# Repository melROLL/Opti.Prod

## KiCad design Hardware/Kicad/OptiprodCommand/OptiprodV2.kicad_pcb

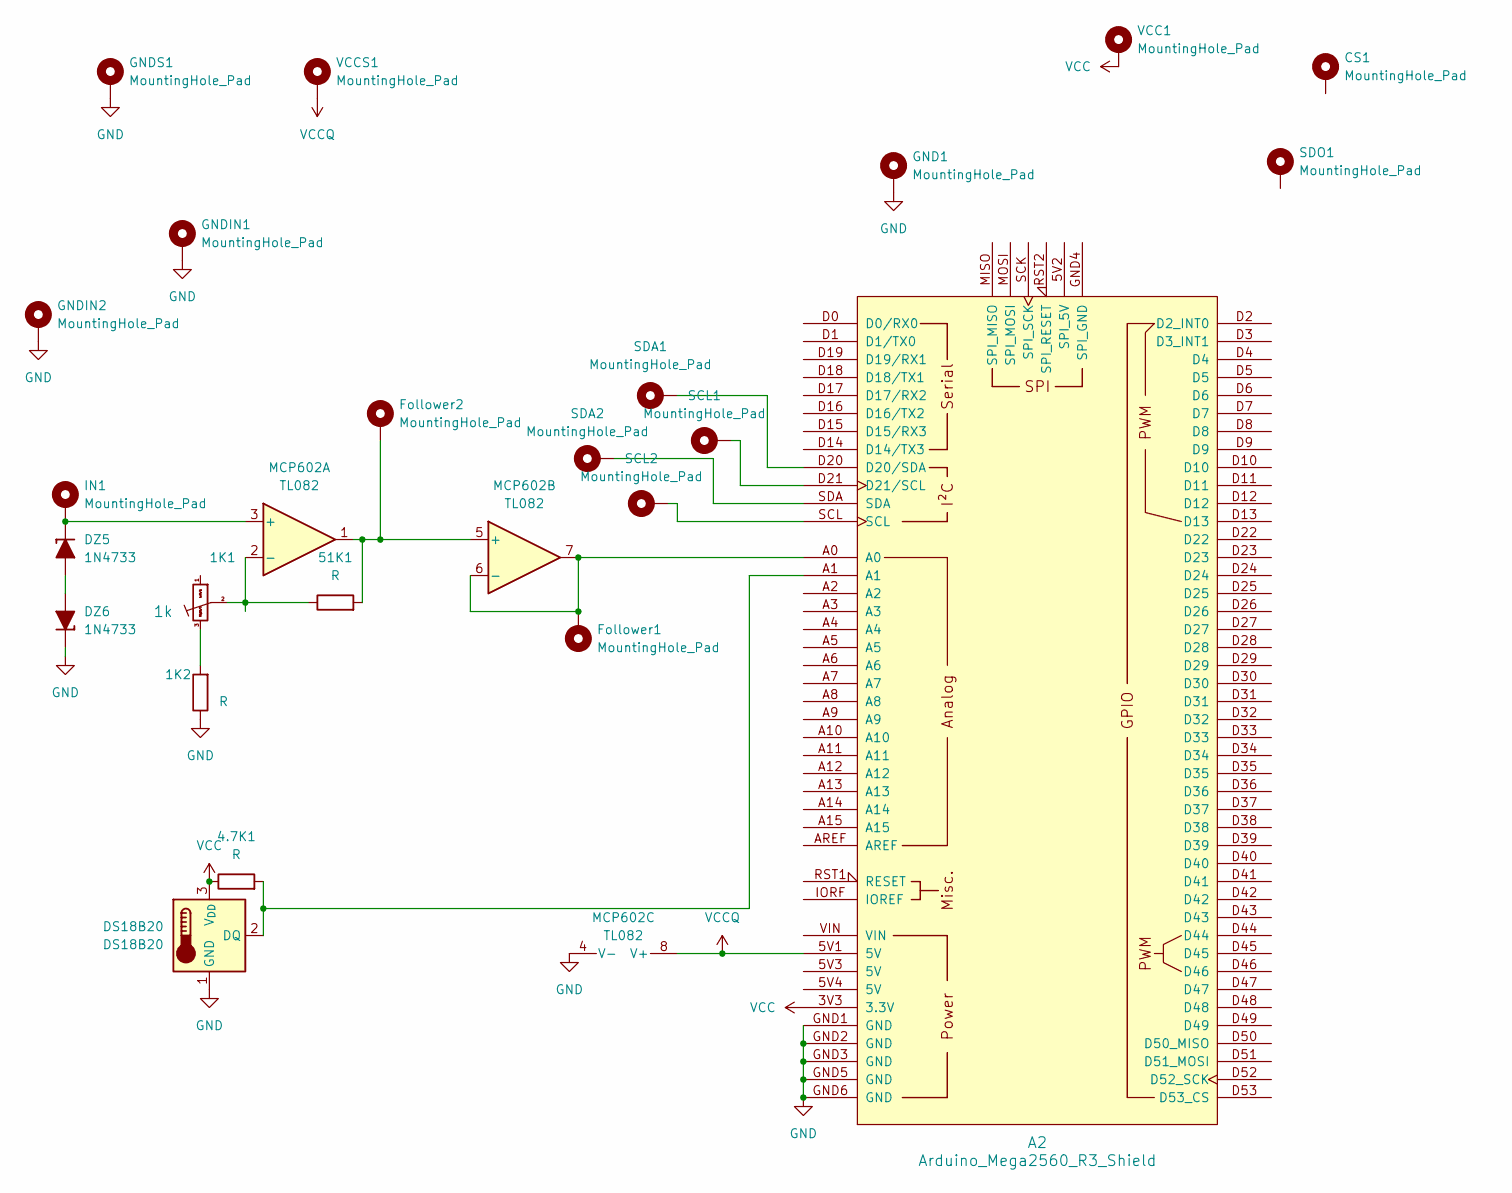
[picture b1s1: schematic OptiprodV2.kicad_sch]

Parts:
1K1: TrimPot_T73YEt_1k; Potentiometer_Bourns_3296W_Vertical; Part Number T73YE102KT20
1K2, 4.7K1, 51K1: R; R_Axial_DIN0204_L3.6mm_D1.6mm_P7.62mm_Horizontal
A2: Arduino_Mega2560_R3_Shield
CS1: MountingHole_Pad; Pin_D1.0mm_L10.0mm
DS18B20: DS18B20; TO-92_Inline_Wide
DZ5, DZ6: 1N4733; D_A-405_P12.70mm_Horizontal
Follower1, Follower2: MountingHole_Pad; Pin_D1.0mm_L10.0mm
GND1: MountingHole_Pad; Pin_D1.0mm_L10.0mm
GNDIN1, GNDIN2: MountingHole_Pad; Pin_D1.0mm_L10.0mm
GNDS1: MountingHole_Pad; Pin_D1.0mm_L10.0mm
IN1: MountingHole_Pad; Pin_D1.0mm_L10.0mm
MCP602: TL082; DIP-8_W7.62mm
SCL1, SCL2: MountingHole_Pad; Pin_D1.0mm_L10.0mm
SDA1, SDA2: MountingHole_Pad; Pin_D1.0mm_L10.0mm
SDO1: MountingHole_Pad; Pin_D1.0mm_L10.0mm
VCC1: MountingHole_Pad; Pin_D1.0mm_L10.0mm
VCCS1: MountingHole_Pad; Pin_D1.0mm_L10.0mm

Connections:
GND: 1K2.1, A2.GND1 (GND), A2.GND2 (GND), A2.GND3 (GND), A2.GND5 (GND), A2.GND6 (GND), DS18B20.1 (GND), DZ6.1 (K), GND1.1, GNDIN1.1, GNDIN2.1, GNDS1.1, MCP602.4 (V-)
unnamed: 1K1.2 (Center), 51K1.1, MCP602.2 (-)
unnamed: 1K1.3 (Right), 1K2.2
unnamed: A2.D20 (D20/SDA), SDA1.1
unnamed: A2.D21 (D21/SCL), SCL1.1
unnamed: A2.SCL, SCL2.1
unnamed: A2.SDA, SDA2.1
unnamed: 4.7K1.2, A2.A1, DS18B20.2 (DQ)
unnamed: DZ5.2 (A), DZ6.2 (A)
unnamed: DZ5.1 (K), IN1.1, MCP602.3 (+)
unnamed: 51K1.2, Follower2.1, MCP602.1, MCP602.5 (+)
unnamed: A2.A0, Follower1.1, MCP602.6 (-), MCP602.7
VCC: 4.7K1.1, A2.3V3 (3.3V), DS18B20.3 (V_{DD}), VCC1.1
VCCQ: A2.5V1 (5V), MCP602.8 (V+), VCCS1.1

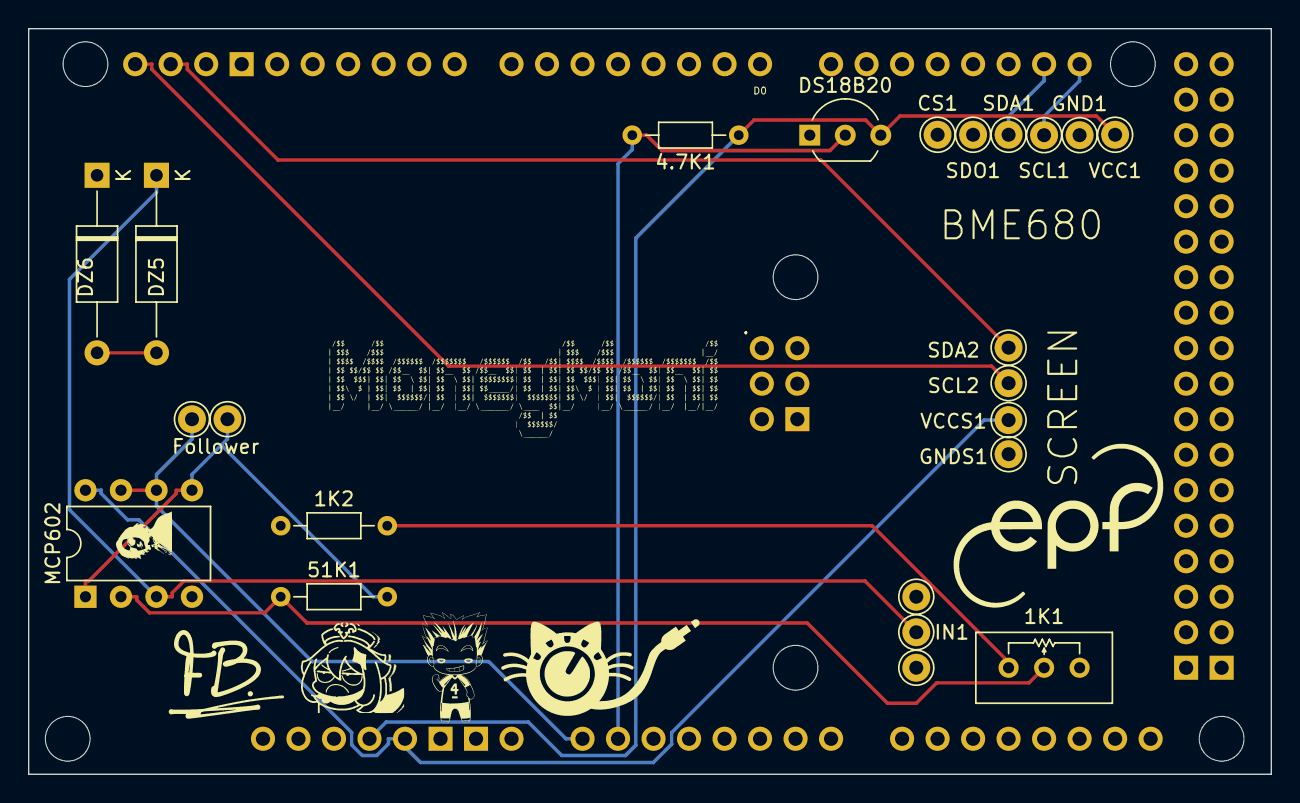
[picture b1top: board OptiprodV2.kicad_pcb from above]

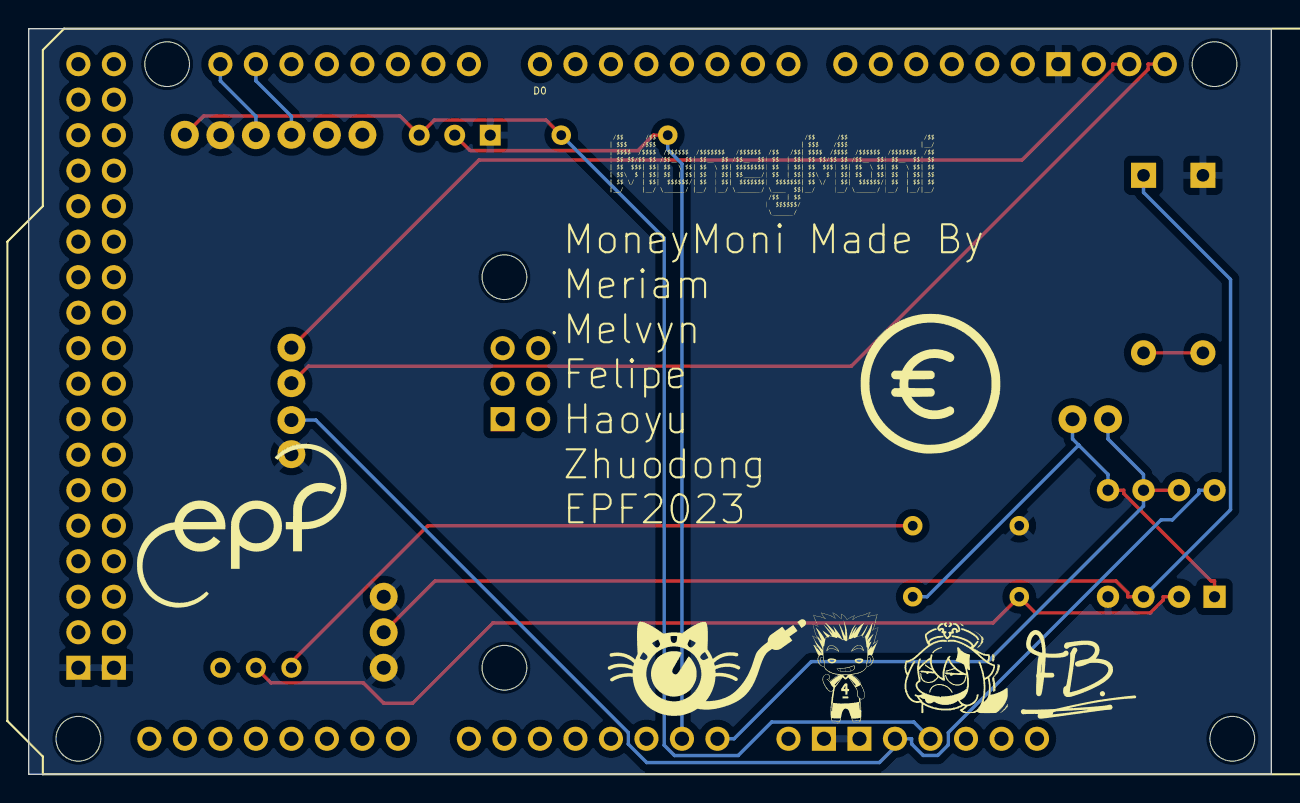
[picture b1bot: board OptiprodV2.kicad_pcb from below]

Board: 2 copper layers, 88.9 x 53.3 mm, 37 parts (7 on the bottom side), 14 nets.

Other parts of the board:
G:jgggjfuy: LOGO; ZHK8MM
G:jgggjfuykjfèdtrdètuvf_yvc: LOGO; ZHK8MM
Ghhhgfcccdcdfcfgvfvfvdfcxdrdsqaqhjgugctyv: LOGO; Moneymoney25
Gjchfmljkgjhv: LOGO; Haoyu8MM
I IUG UYGHIUNIJ?CU NC4R3H44IRB: LOGO; FelipeBarbaste10mm
KJHHIB9UYG 8TBYFI TG8Y : LOGO; EPFLOGO15MM
azertyuxcvbngfdsqzert: LOGO; EPFLOGO15MM
eopjohkbihvçh,&iàéahihazdnçià?ADZO0IERZGDSQHJ32GN0JCH3 0KCINR39XNGZHENCHZUNVYHIUNHC2NIUN3: LOGO; Moneymoney30
ggfrtdrdpopop: LOGO; Haoyu8MM
hhfttyhgfdssaazzqwxcvbn,kpo: LOGO; eurologo
khojhvgvgvjhbhjvuuuzuaanhhsrrsnnf1456789876432112345678765432123467U8765432123456765432134567UI: LOGO; 15mmlogoRW.kicadnonreverse_mod
pjbiçh u_tftf: LOGO; FelipeBarbaste10mm
uhuhh: LOGO; 15mmlogoRW.kicadnonreverse_mod

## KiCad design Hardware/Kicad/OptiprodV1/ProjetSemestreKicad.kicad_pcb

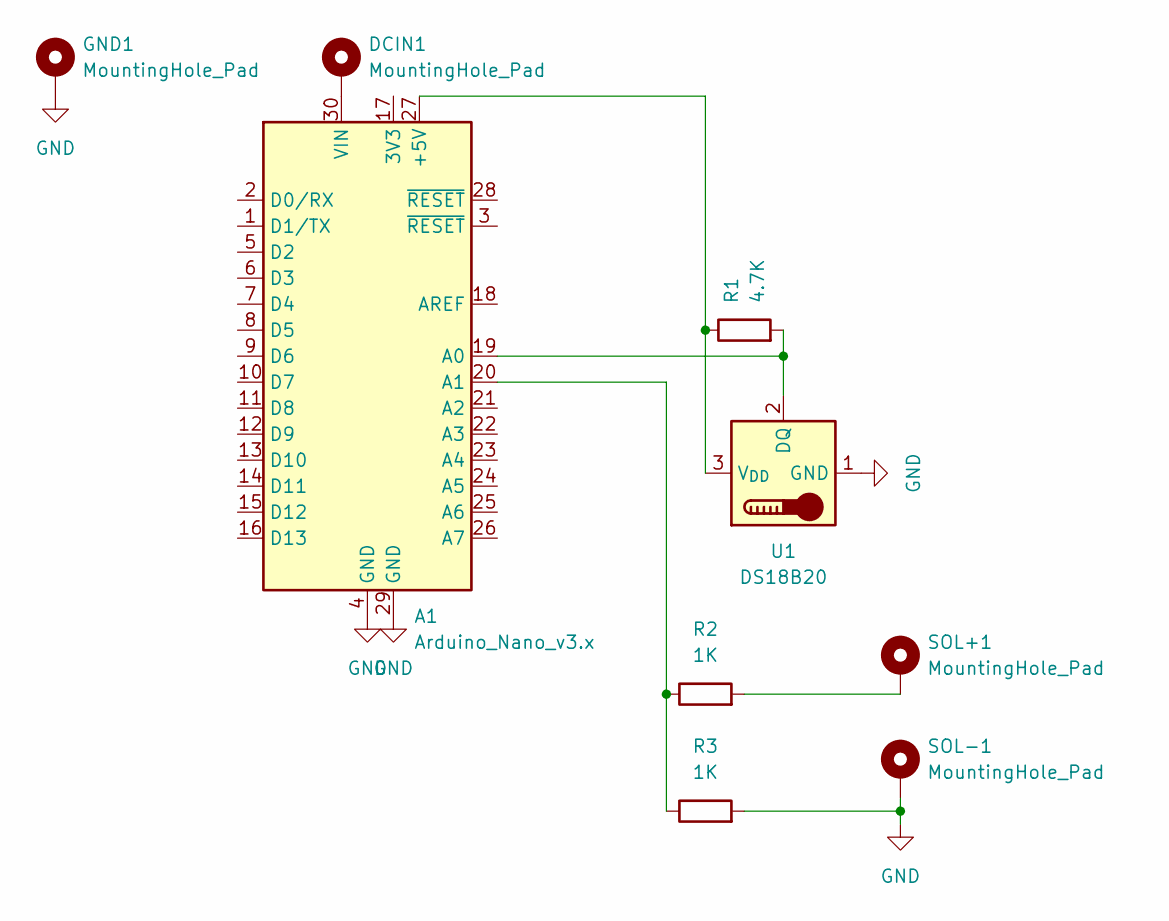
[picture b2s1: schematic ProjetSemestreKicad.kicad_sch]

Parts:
A1: Arduino_Nano_v3.x; Arduino_Nano
DCIN1: MountingHole_Pad; Pin_D1.0mm_L10.0mm
GND1: MountingHole_Pad; Pin_D1.0mm_L10.0mm
R1: 4.7K; R_Axial_DIN0207_L6.3mm_D2.5mm_P7.62mm_Horizontal
R2, R3: 1K; R_Axial_DIN0207_L6.3mm_D2.5mm_P7.62mm_Horizontal
SOL+1: MountingHole_Pad; Pin_D1.0mm_L10.0mm
SOL-1: MountingHole_Pad; Pin_D1.0mm_L10.0mm
U1: DS18B20; TO-92_Inline

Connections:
GND: A1.4 (GND), A1.29 (GND), GND1.1, R3.2, SOL-1.1, U1.1 (GND)
unnamed: A1.27 (+5V), R1.1, U1.3 (V_{DD})
unnamed: A1.19 (A0), R1.2, U1.2 (DQ)
unnamed: A1.20 (A1), R2.1, R3.1
unnamed: A1.30 (VIN), DCIN1.1
unnamed: R2.2, SOL+1.1

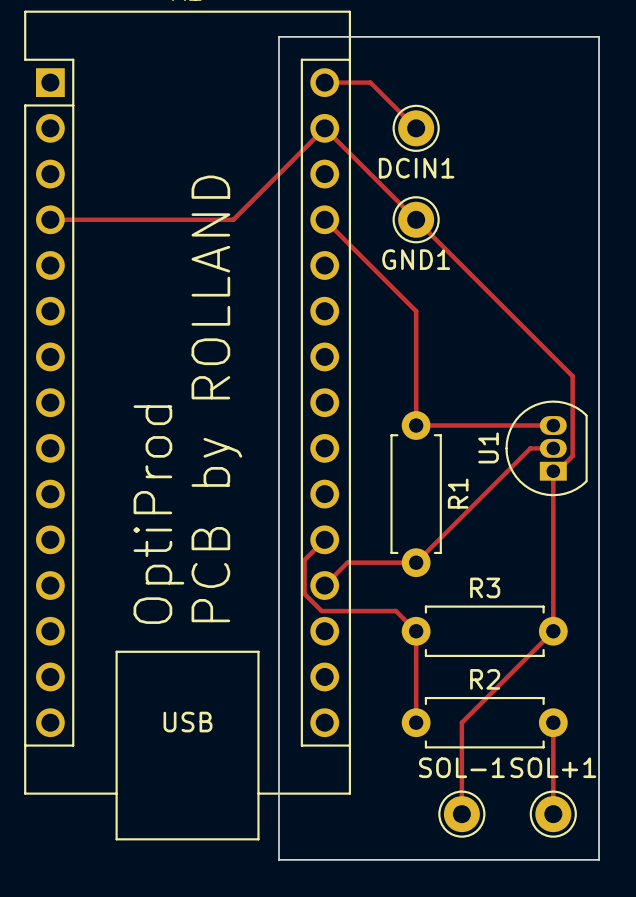
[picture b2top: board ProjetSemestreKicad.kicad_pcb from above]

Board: 2 copper layers, 17.8 x 45.7 mm, 9 parts (0 on the bottom side), 6 nets.

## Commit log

2023-09-14 filesadded
2023-09-14 first commitement
2023-09-14 code translated to english
2023-09-15 Modern_art_added
2023-09-15 codes updated
2023-09-15 Kicadupdated
2023-09-21 propertyforvscodearduinocompilation
2023-09-21 new spec
2023-09-25 SpecAndPoc
2023-09-25 kicadupdate
2023-09-25 commit2.2.1
2023-10-12 updatekicad
2023-10-12 add modbus communication working code + documentation
2023-10-12 add temp sensor code combined with modbus
2023-10-12 modified_kicad
2023-10-13 mods
2023-10-13 make the code of the communication cleaner and add other variables
2023-10-16 moded
2023-10-19 software push
2023-10-19 modifiedkicad
2023-10-26 PCBFinished?
2023-10-26 modifiedPCB
2023-10-26 pcbmodified
2023-10-27 PCBFinishedforreal??
2023-10-27 stupidnameforcommit
2023-10-27 codesformeriam
2023-10-27 add flux sensor code
2023-10-27 stencilcreated
2023-10-27 gerberforJLCPCBmade
2023-10-27 add the working code of the screen,flux sensor,temp sensor and with modbus connection
2023-10-27 add the test version for mac
2023-10-27 software comunication finished, enter debugging step.
2023-10-27 PCBlastCommit?
2023-10-27 kdsv
2023-10-27 kjghkjsf
2023-11-24 add second temp sensor
2023-11-24 kicad_update
2023-11-30 correctedKicad
2023-11-30 hjftyg
2023-12-01 commiting to the project
2023-12-07 add email code
2023-12-07 hgygzd
2023-12-20 boxadded
2023-12-21 readyforproduction!!!!!!
2024-01-11 cadmodelingupdate
2024-01-12 rail mount added
2024-01-13 realeseforclient
2024-01-15 Cad Changed
2024-01-15 Add files via upload
    final version of application, exe file and source code.
2024-01-15 software release
2024-01-15 final arduino code
2024-01-15 clean realease for Laurent
